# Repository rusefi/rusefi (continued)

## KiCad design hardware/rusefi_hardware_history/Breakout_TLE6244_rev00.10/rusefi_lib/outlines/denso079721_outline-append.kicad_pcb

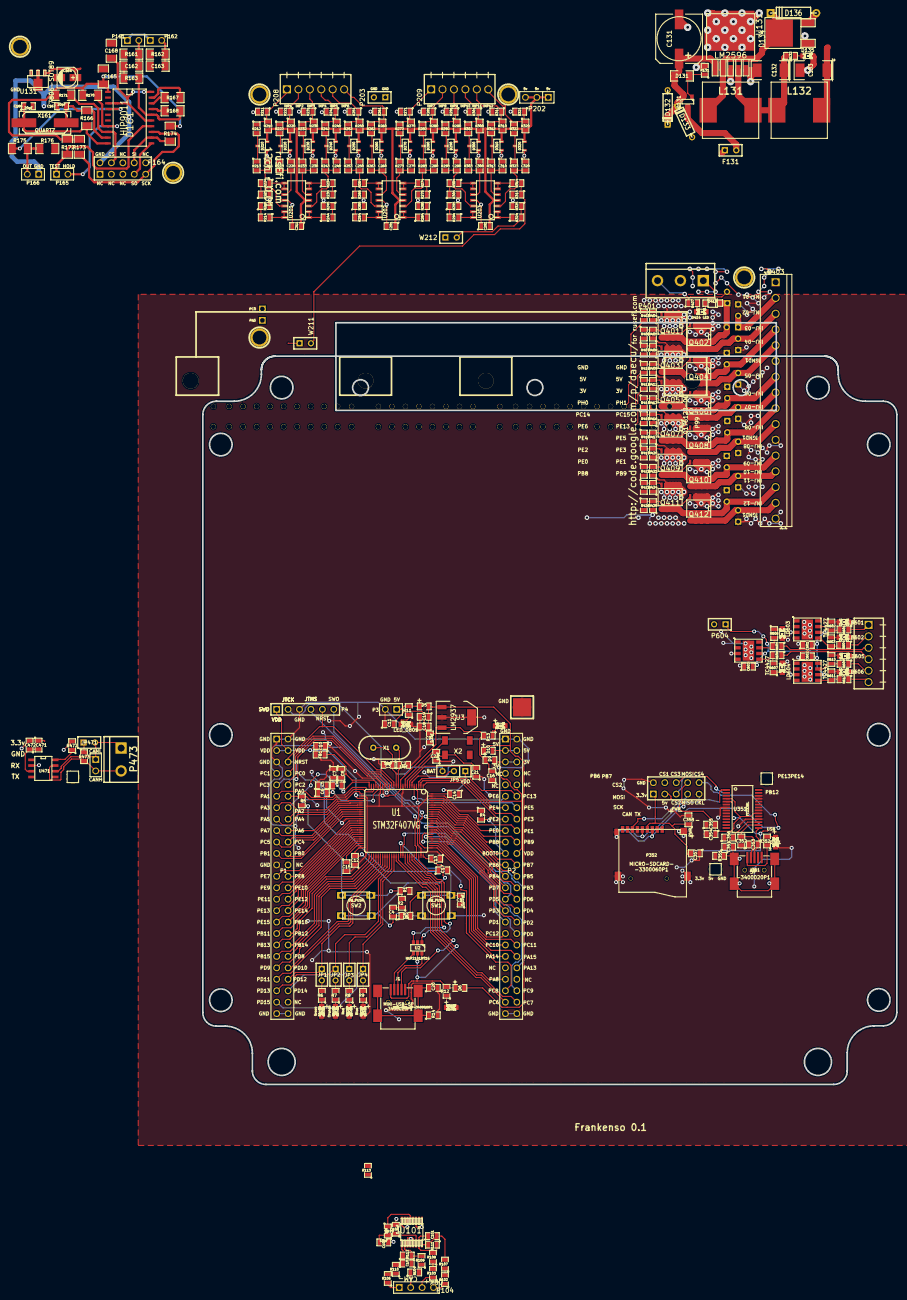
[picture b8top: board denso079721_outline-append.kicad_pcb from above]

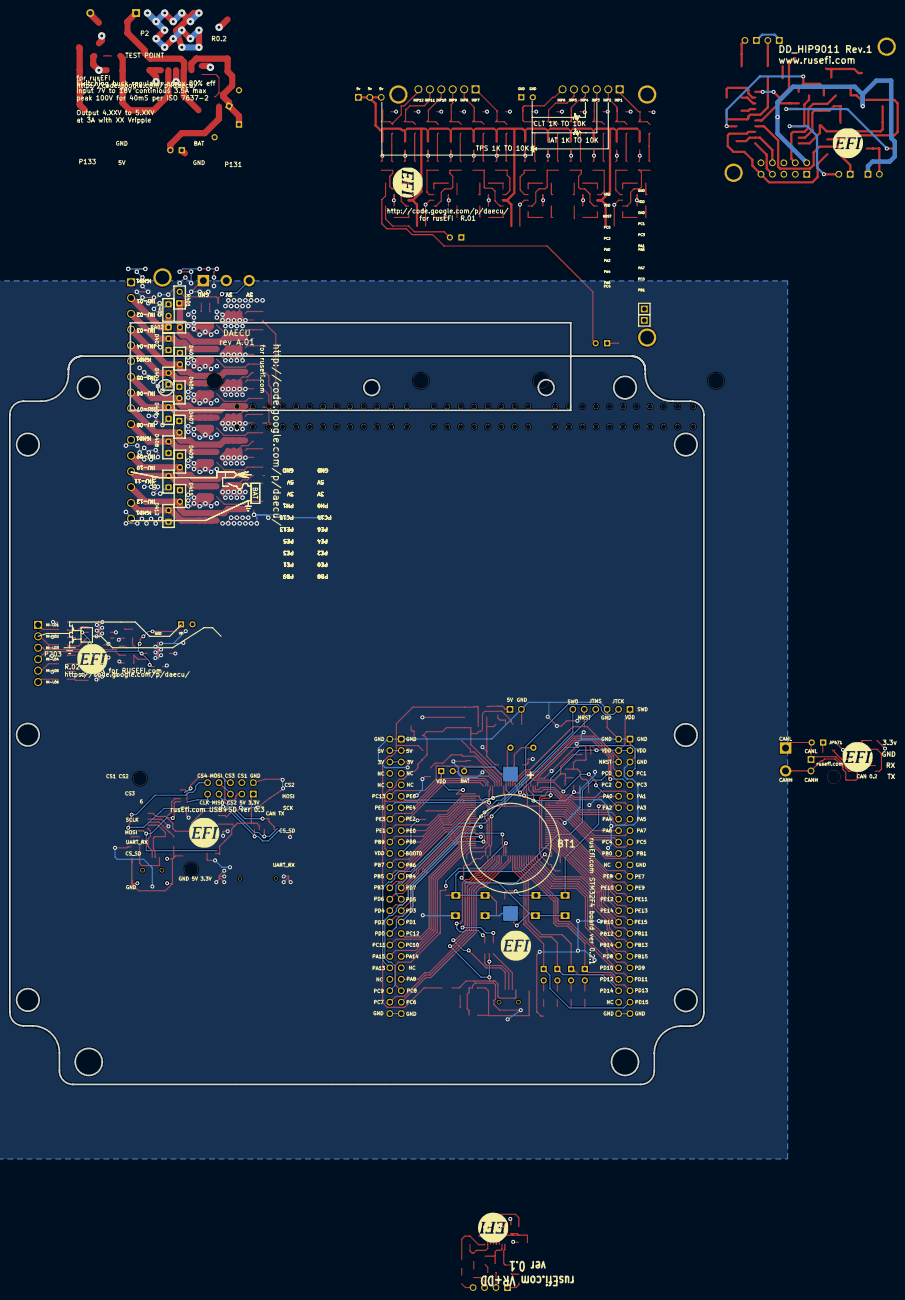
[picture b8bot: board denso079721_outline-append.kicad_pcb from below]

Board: 2 copper layers, 358 parts (24 on the bottom side), 255 nets.

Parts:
BT1: BATTERY_CR2032; BATT_CR2032_MPD
C1: 0.02uF; SM0805
C2, C3, C21, C22: 18pF; SM0805
C4, C15, C17: 2u2F; SM0805
C5, C8, C210, C220, C230, C240, C250, C260, C270, C280, C290, C300, C310, C320: 0.01uF; SM0805
C6, C7, C16: 1uF; SM0805
C9, C10, C11, C12, C13, C14, C18, C20, C104, C211, C251, C291, C601, C602, C603: 0.1uF; SM0805
C19, C354, C358, C472: 4.7uF; SM0805
C101, C102: 1000pF; SM0805
C103: 10uF; SM0805
C131: 470uF 25V; SMDSVP10
C132, C133: 220uF 16V; SM2512
C162, C163: 47n; SM1206
C164: 10u; c_elec_4x5.3
C165: 100n; SM1206
C166, C167: 20pF; SM0805
C168: 22n; SM1206
C351: 4700pF; SM0805
C352, C353: 47pF; SM0805
C355, C356, C357, C471: .1uF; SM0805
D1, D2, D3, D4, D7, D8, D11: LED_0805; LED-0805_A
D5, D6, D9, D10: DIODESCH; SM0805-diode
D131: ZENERSMALL; SM1206
D132, D133: TVS; D133
D134: SCHDPAK; DPAK2
D135: GREEN; LED-0805
D136: DIODESCH; D134
D161: HIP9011; SO20L
D210, D220, D230, D240, D250, D260, D270, D280, D290, D300, D310, D320: DOUBLE_SCHOTTKY; sot23
D351: GREEN; LED-0805_A
D401, D402, D403, D404, D405, D406, D407, D408, D409, D410, D411, D412: DIODE; SIL-2
D413: DIODE; SOD-123
D414: LED; LED-0805
F131: 3.5A; SIL-2
FB1: FILTER; SM0805
G1, G101, G161, G201, G305, G471, G601: LOGO; LOGO_F
J1, J351: MINI-USB-5P-3400020P1
JP1, JP2, JP3, JP4, JP471: JUMPER; JUMPER-2
JP5: JUMPER3; SIL-3
L131, L132: 38uH; SM100uH
LD601, LD602, LD603, LD604, LD605, LD606: LED; LED-0805
M200, M201, M202, M401: CONN_1; 1pin
M351, M352, M471: CONN_1; PIN_ARRAY_1
P1, P2: CONN_25X2; PIN_ARRAY_25x2_A
P3, P472: CONN_2; PIN_ARRAY_2_A
P4: CONN_6; PIN_ARRAY-6X1
P5: CONN_1; 1PIN_SMD
P99: 0176122-06; 176122-6
P104: CONN_4; PIN_ARRAY_4x1
P161: KNOCK 1; PIN_ARRAY_2X1
P162: KNOCK 2; PIN_ARRAY_2X1
P164: CONN_5X2; PIN_ARRAY_5x2
P165, P166: CONN_2; PIN_ARRAY_2X1
P202: CONN_3; PIN_ARRAY_3X1
P203, P604: CONN_2; SIL-2
P204, P205: CONN_1; PIN_ARRAY_1
P208, P209: CONN_6; 6_screw_term_.1in
P351: CONN_5X2; PIN_ARRAY_5x2_M
P352: MICRO-SDCARD-CONNECTOR-3300060P1
P401: CONN_3; bornier3
P403: CONN_16; SIL-16_3.5MM
P473: CONN_2; bornier2
P603: CONN_6; OSTVN06A150
Q131: MOS_PRO; SOT23
Q401, Q402, Q403, Q404, Q405, Q406, Q407, Q408, Q409, Q410, Q411, Q412: OVP_DRIVER; SO8E_ST
R1, R3, R4, R113, R114, R212, R222, R232, R242, R252, R262, R272, R282, R292, R302, R312, R322, R472: 10k; SM0805
R2: 100R; SM0805
R5: 330R; SM0805
R6, R7, R8, R9: 680R; SM0805
R10: 47R; SM0805
R11, R12, R13, R131, R132, R352: 1k; SM0805
R14: 100k; SM0805
R102, R103, R104, R106, R107, R108, R109, R110, R111, R112: 5k; SM0805
R161, R162, R166: 1M; SM1206
R163, R175, R176: 10k; SM1206
R167, R168: 68k; SM1206
R170, R171, R172, R173, R174: 1K; SM1206
R210, R220, R230, R240, R250, R260, R270, R280, R290, R300, R310, R320, R602, R603, R606, R607, R610, R611: 2700; SM0805
R211, R221, R231, R241, R251, R261, R271, R281, R291, R301, R311, R321: 500K; SM0805
R213, R223, R233, R243, R253, R263, R273, R283, R293, R303, R313, R323, R601, R604, R605, R608, R609, R612: 100; SM0805
R214, R215, R224, R225, R234, R235, R244, R245, R254, R255, R264, R265, R274, R275, R284, R285, R294, R295, R304, R305, R314, R315, R324, R325: 1500; SM0805
R351: 1M; SM0805
R401: OPT; SIL-2
R402: 0R; SIL-2
R403, R406, R407, R410, R411, R414, R415, R418, R419, R422, R423, R426: 20R; SM0805
R404, R405, R408, R409, R412, R413, R416, R417, R420, R421, R424, R425, R427: 1K; SM0805
R473: 120; SM0805
SW1, SW2: SW_PUSH; TL-1105
U1: STM32F407VG; TQFP_100
U2: NUF2101MT1G; SOT-457
U3: LM2937; SOT223
U101: MAX9926/9927; maxim-10-QSOP16
U131: LM2596; DPAK5
U131#2: 7805-SOT89; sot89
U201, U202, U203: LMV324IDR; so-14
U351: FT232RL; ssop-28
U471: SN65HVD230; SO8E
U601, U602, U603: TC4427; SOIC8-DFN
W211, W212: TEST; SIL-2
X1: CRYSTAL; HC-49V
X2: CRYSTAL(MC306); MC-306
X161: QUARTZ; Q_49U3HMS

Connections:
/3.3V: C357.2, C358.1, C471.2, C472.1, D9.2, P2.5, P2.6, P351.1, P352.4, P401.2, U471.3
/5V: C103.2, C104.1, C133.1, C211.1, C251.1, C291.2, C354.1, C355.2, D10.2, D210.3, D220.3, D230.3, D240.3, D250.3, D260.3, D270.3, D280.3, D290.3, D300.3, D310.3, D320.3, L132.2, P2.3, P2.4, P202.1, P202.2, P202.3, P351.3, P401.3, R113.1, R114.2, R210.2, R220.2, R230.2, R240.2, R250.2, R260.2, R270.2, R280.2, R290.2, R300.2, R310.2, R320.2, R401.2, R427.1, U101.14, U201.4, U202.4, U203.4, U351.4, U351.20
/5Vi: C18.2, C19.1, D5.2, D6.2, D10.1, U3.1
/+5V: C165.1, D161.1, R170.1, R171.1, R172.1, R173.1, R174.1
/BOOT0: P2.21, R4.2, U1.94
/CAM: R114.1, U101.5
/CAM+: P104.1, R106.1
/CAM-: P104.2, R104.1
/CANH: P472.2, P473.2, R473.2, U471.7
/CANL: JP471.2, P472.1, P473.1, U471.6
/CRANK: R113.2, U101.4
/CRK2+: P104.4, R102.1
/CRK2-: P104.3, R103.1
/CS: D161.8, P164.4, R171.2
/D+: C353.2, J1.3, J351.3, U2.6, U351.15
/D-: C352.2, J1.2, J351.2, U2.4, U351.16
/FB: C132.1, L131.2, L132.1, R132.1, U131.4
/GND: C164.2, C165.2, C166.2, C167.2, C168.2, D161.2, P161.1, P162.1, P164.2, P166.1, R161.2, R162.2, R176.2, U131#2.2
/HL1: P603.1, R601.1
/HL2: P603.2, R604.1
/HL3: P603.3, R605.1
/HL4: P603.4, R608.1
/HL5: P603.5, R609.1
/HL6: P603.6, R612.1
/INJ-01: D413.2, Q401.2, R401.1, R402.2
/INJ-01_2: D401.2, P403.2, R402.1
/INJ-02: D402.2, P403.3, Q402.2
/INJ-03: D403.2, P403.4, Q403.2
/INJ-04: D404.2, P403.5, Q404.2
/INJ-05: D405.2, P403.7, Q405.2
/INJ-06: D406.2, P403.8, Q406.2
/INJ-07: D407.2, P403.9, Q407.2
/INJ-08: D408.2, P403.10, Q408.2
/INJ-09: D409.2, P403.12, Q409.2
/INJ-10: D410.2, P403.13, Q410.2
/INJ-11: D411.2, P403.14, Q411.2
/INJ-12: D412.2, P403.15, Q412.2
/INP1: P208.1, R210.1, R211.1, R212.1
/INP2: P208.2, R220.1, R221.1, R222.1
/INP3: P208.3, R230.1, R231.1, R232.1
/INP4: P208.4, R240.1, R241.1, R242.1
/INP5: P208.5, R250.1, R251.1, R252.1
/INP6: P208.6, R260.1, R261.1, R262.1
/INP7: P209.1, R270.1, R271.1, R272.1
/INP8: P209.2, R280.1, R281.1, R282.1
/INP9: P209.3, R290.1, R291.1, R292.1
/INP10: P209.4, R300.1, R301.1, R302.1
/INP11: P209.5, R310.1, R311.1, R312.1
/INP12: P209.6, R320.1, R321.1, R322.1
/INT/HLD: D161.7, P165.2, R170.2
/INTOUT: D161.4, R175.1
/NRST: C1.2, P1.6, P4.5, R3.2, SW1.1, U1.14
/OUT: D134.2, D136.2, L131.1, P166.2, R175.2, R176.1, U131.2
/PA0: P1.12, R5.1, R254.2, R255.1, U1.23
/PA1: P1.11, R214.2, R215.1, U1.24
/PA2: P1.14, R284.2, R285.1, U1.25
/PA3: P1.13, R224.2, R225.1, U1.26
/PA4: P1.16, R274.2, R275.1, U1.29
/PA5: P1.15, P204.1, U1.30
/PA6: P1.18, R294.2, R295.1, U1.31
/PA7: P1.17, R304.2, R305.1, U1.32
/PA8: P2.43, U1.67
/PA9: D6.1, J1.1, R12.2, U1.68, U2.5
/PA10: J1.4, U1.69
/PA11: U1.70, U2.3
/PA12: U1.71, U2.1
/PA13: P2.42, P4.4, U1.72
/PA14: P2.39, P4.2, U1.76
/PA15: P2.40, U1.77
/PB0: P1.22, U1.35
/PB1: P1.21, U1.36
/PB3: P2.28, P4.6, P351.9, P352.5, U1.89
/PB4: P2.25, P351.7, P352.7, U1.90
/PB5: P2.26, P351.8, P352.3, U1.91
/PB6: P2.23, U1.92, U471.1
/PB7: P2.24, U1.93
/PB8: P2.19, R423.2, U1.95
/PB9: P2.20, R426.2, U1.96
/PB10: P1.34, U1.47
/PB11: P1.35, U1.48
/PB12: P1.36, U1.51, U471.4
/PB13: P1.37, U1.52
/PB14: P1.38, U1.53
/PB15: P1.39, U1.54
/PC0: P1.8, P205.1, U1.15
/PC1: P1.7, R244.2, R245.1, U1.16
/PC2: P1.10, R264.2, R265.1, U1.17
/PC3: P1.9, R234.2, R235.1, U1.18
/PC4: P1.20, U1.33, W211.1
/PC5: P1.19, U1.34, W212.1
/PC6: P2.47, U1.63
/PC7: P2.48, U1.64, U603.2
/PC8: P2.45, U1.65
/PC9: P2.46, U1.66, U603.4
/PC10: P2.37, U1.78, U351.5
/PC11: P2.38, U1.79, U351.1
/PC12: P2.35, U1.80
/PC13: P2.12, R410.2, U1.7
/PD0: P2.36, U1.81
/PD1: P2.33, U1.82
/PD2: P2.34, U1.83
/PD3: P2.31, U1.84
/PD4: P2.32, P352.2, U1.85
/PD5: P2.29, U1.86
/PD6: P2.30, U1.87
/PD7: P2.27, U1.88
/PD8: P1.40, U1.55
/PD9: P1.41, U1.56
/PD10: P1.42, U1.57
/PD11: P1.43, U1.58
/PD12: JP1.1, P1.44, U1.59
/PD13: JP2.1, P1.45, U1.60
/PD14: JP3.1, P1.46, U1.61
/PD15: JP4.1, P1.47, U1.62
/PE0: P2.17, R419.2, U1.97
/PE1: P2.18, R422.2, U1.98
/PE2: P2.15, R415.2, U1.1
/PE3: P2.16, R418.2, U1.2
/PE4: P2.13, R411.2, U1.3
/PE5: P2.14, R414.2, U1.4
/PE6: P2.11, R407.2, U1.5
/PE7: P1.25, U1.38
/PE8: P1.26, U1.39, U601.4
/PE9: P1.27, U1.40
/PE10: P1.28, U1.41, U602.2
/PE11: P1.29, U1.42
/PE12: P1.30, U1.43, U601.2
/PE13: P1.31, U1.44
/PE14: P1.32, U1.45, U602.4
/PE15: P1.33, U1.46
/SCK: D161.13, P164.9, R173.2
/SI: D161.12, P164.8, R174.2
/SO: D161.11, P164.7
/TEST: D161.14, P165.1, R172.2
/VBAT: C131.1, D131.2, D132.2, D133.2, Q131.2, U131.1
/VDD: C4.1, C9.2, C10.2, C11.2, C12.2, C13.2, C14.2, C16.2, D9.1, FB1.2, JP5.1, P1.3, P1.4, P2.22, P4.1, R3.1, R13.2, SW2.2, U1.11, U1.19, U1.28, U1.50, U1.75, U1.100, U3.3
/VP: C601.2, C602.2, C603.2, P604.1, U601.6, U602.6, U603.6
/Vf: F131.2, Q131.3
F-000087: C3.1, U1.13, X1.1
F-000088: C17.1, U1.73
F-000089: C2.1, U1.12, X1.2
F-000090: C15.1, U1.49
F-000091: C7.2, C8.2, FB1.1, R10.1, U1.22
F-000092: JP5.2, U1.6
F-000093: BT1.1, JP5.3
F-000094: C4.2, R2.1
F-000095: R1.1, R2.2, R5.2, SW2.1
F-000096: JP3.2, R8.2
F-000097: JP4.2, R9.2
F-000098: JP1.2, R6.2
F-000099: JP2.2, R7.2
F-0000100: D7.1, R11.1
F-0000101: D5.1, P3.1, R11.2
F-0000102: D8.1, R12.1
F-0000103: D2.1, R7.1
F-0000104: D3.1, R8.1
F-0000105: D4.1, R9.1
F-0000106: D11.1, R13.1
F-0000107: C20.1, J1.6, R14.1
F-0000108: C5.2, C6.2, R10.2, U1.21
F-0000109: D1.1, R6.1
F-0000110: C21.2, U1.8, X2.1
F-0000111: C22.2, U1.9, X2.4
F-0000129: R102.2, R107.1
F-0000130: R104.2, R109.1
F-0000132: R106.2, R110.1
F-0000133: R103.2, R108.1
F-0000134: C101.1, R108.2, R111.1, U101.15
F-0000135: C101.2, R107.2, R111.2, U101.16
F-0000136: C102.1, R110.2, R112.1, U101.9
F-0000137: C102.2, R109.2, R112.2, U101.10
F-0000144: D131.1, Q131.1, R131.1
F-0000145: D135.1, R132.2
F-0000155: C167.1, D161.9, R166.2, X161.2
F-0000156: C163.1, P162.2, R162.1
F-0000158: C166.1, D161.10, R166.1, X161.1
F-0000159: C168.1, D161.3, D161.15, D161.20
F-0000160: D161.16, R163.2, R168.2
F-0000161: D161.17, R168.1
F-0000162: D161.18, R167.1
F-0000163: D161.19, R167.2
F-0000164: C162.2, R163.1
F-0000165: C162.1, P161.2, R161.1
F-0000167: C164.1, U131#2.1
F-0000192: D280.2, R282.2, R283.1
F-0000193: R214.1, U201.13, U201.14
F-0000194: R224.1, U201.8, U201.9
F-0000195: D270.2, R272.2, R273.1
F-0000196: R244.1, U201.1, U201.2
F-0000197: D300.2, R302.2, R303.1
F-0000198: D290.2, R292.2, R293.1
F-0000199: R304.1, U203.8, U203.9
F-0000200: R294.1, U203.13, U203.14
F-0000201: C290.2, R293.2, U203.12
F-0000202: D250.2, R252.2, R253.1
F-0000203: C300.2, R303.2, U203.10
F-0000204: R314.1, U203.6, U203.7
F-0000205: R324.1, U203.1, U203.2
F-0000206: C310.2, R313.2, U203.5
F-0000207: C320.2, R323.2, U203.3
F-0000208: D320.2, R322.2, R323.1
F-0000209: D260.2, R262.2, R263.1
F-0000210: D310.2, R312.2, R313.1
F-0000211: R324.2, R325.1, W212.2
F-0000212: R314.2, R315.1, W211.2
F-0000213: C250.2, R253.2, U202.12
F-0000214: D210.2, R212.2, R213.1
F-0000215: R254.1, U202.13, U202.14
F-0000216: R274.1, U202.6, U202.7
F-0000217: R264.1, U202.8, U202.9
F-0000218: C240.2, R243.2, U201.3
F-0000219: C230.2, R233.2, U201.5
F-0000220: C270.2, R273.2, U202.5
F-0000221: C280.2, R283.2, U202.3
F-0000222: C220.2, R223.2, U201.10
F-0000223: D220.2, R222.2, R223.1
F-0000224: C210.2, R213.2, U201.12
F-0000225: C260.2, R263.2, U202.10
F-0000226: R284.1, U202.1, U202.2
F-0000227: D240.2, R242.2, R243.1
F-0000229: D230.2, R232.2, R233.1
F-0000230: R234.1, U201.6, U201.7
F-0000249: J351.1, R352.1
F-0000250: C351.2, J351.6, R351.1
F-0000251: D351.1, R352.2
F-0000270: C356.2, U351.17
F-0000312: Q408.1, R417.2, R418.1
F-0000313: Q404.1, R409.2, R410.1
F-0000314: Q406.1, R413.2, R414.1
F-0000315: Q402.1, R405.2, R406.1
F-0000316: D414.1, R427.2
F-0000317: Q410.1, R421.2, R422.1
F-0000318: D413.1, D414.2
F-0000319: Q412.1, R425.2, R426.1
F-0000320: Q401.1, R403.1, R404.2
F-0000321: Q405.1, R411.1, R412.2
F-0000322: Q403.1, R407.1, R408.2
F-0000323: Q409.1, R419.1, R420.2
F-0000324: Q407.1, R415.1, R416.2
F-0000325: Q411.1, R423.1, R424.2
F-0000332: JP471.1, R473.1
F-0000333: R472.1, U471.8
F-0000347: LD604.1, R607.1
F-0000348: LD601.1, R602.1
F-0000349: R609.2, R610.2, U603.7
F-0000350: LD602.1, R603.1
F-0000351: R603.2, R604.2, U601.5
F-0000352: R601.2, R602.2, U601.7
F-0000353: R607.2, R608.2, U602.5
F-0000354: R605.2, R606.2, U602.7
F-0000355: LD606.1, R611.1
F-0000356: R611.2, R612.2, U603.5
F-0000357: LD605.1, R610.1
F-0000358: LD603.1, R606.1
GND: BT1.2, C1.1, C2.2, C3.2, C5.1, C6.1, C7.1, C8.1, C9.1, C10.1, C11.1, C12.1, C13.1, C14.1, C15.2, C16.1, C17.2, C18.1, C19.2, C20.2, C21.1, C22.1, C103.1, C104.2, C131.2, C132.2, C133.2, C210.1, C211.2, C220.1, C230.1, C240.1, C250.1, C251.2, C260.1, C270.1, C280.1, C290.1, C291.1, C300.1, C310.1, C320.1, C351.1, C352.1, C353.1, C354.2, C355.1, C356.1, C357.1, C358.2, C471.1, C472.2, C601.1, C602.1, C603.1, D1.2, D2.2, D3.2, D4.2, D7.2, D8.2, D11.2, D132.1, D133.1, D134.1, D134.3, D135.2, D136.1, D210.1, D220.1, D230.1, D240.1, D250.1, D260.1, D270.1, D280.1, D290.1, D300.1, D310.1, D320.1, D351.2, D401.1, D402.1, D403.1, D404.1, D405.1, D406.1, D407.1, D408.1, D409.1, D410.1, D411.1, D412.1, J1.5, J351.5, LD601.2, LD602.2, LD603.2, LD604.2, LD605.2, LD606.2, P1.1, P1.2, P1.5, P1.23, P1.49, P1.50, P2.1, P2.2, P2.49, P2.50, P3.2, P4.3, P5.1, P203.1, P203.2, P351.2, P352.6, P352.G1, P352.G2, P352.G3, P352.G4, P401.1, P403.1, P403.6, P403.11, P403.16, Q401.3, Q402.3, Q403.3, Q404.3, Q405.3, Q406.3, Q407.3, Q408.3, Q409.3, Q410.3, Q411.3, Q412.3, R1.2, R4.1, R14.2, R131.2, R211.2, R215.2, R221.2, R225.2, R231.2, R235.2, R241.2, R245.2, R251.2, R255.2, R261.2, R265.2, R271.2, R275.2, R281.2, R285.2, R291.2, R295.2, R301.2, R305.2, R311.2, R315.2, R321.2, R325.2, R351.2, R404.1, R405.1, R408.1, R409.1, R412.1, R413.1, R416.1, R417.1, R420.1, R421.1, R424.1, R425.1, R472.2, SW1.2, U1.10, U1.20, U1.27, U1.37, U1.74, U1.99, U2.2, U3.2, U3.4, U101.1, U101.3, U101.6, U101.8, U101.11, U101.12, U101.13, U131.3, U131.5, U201.11, U202.11, U203.11, U351.7, U351.18, U351.21, U351.25, U351.26, U471.2, U601.3, U601.9, U602.3, U602.9, U603.3, U603.9
